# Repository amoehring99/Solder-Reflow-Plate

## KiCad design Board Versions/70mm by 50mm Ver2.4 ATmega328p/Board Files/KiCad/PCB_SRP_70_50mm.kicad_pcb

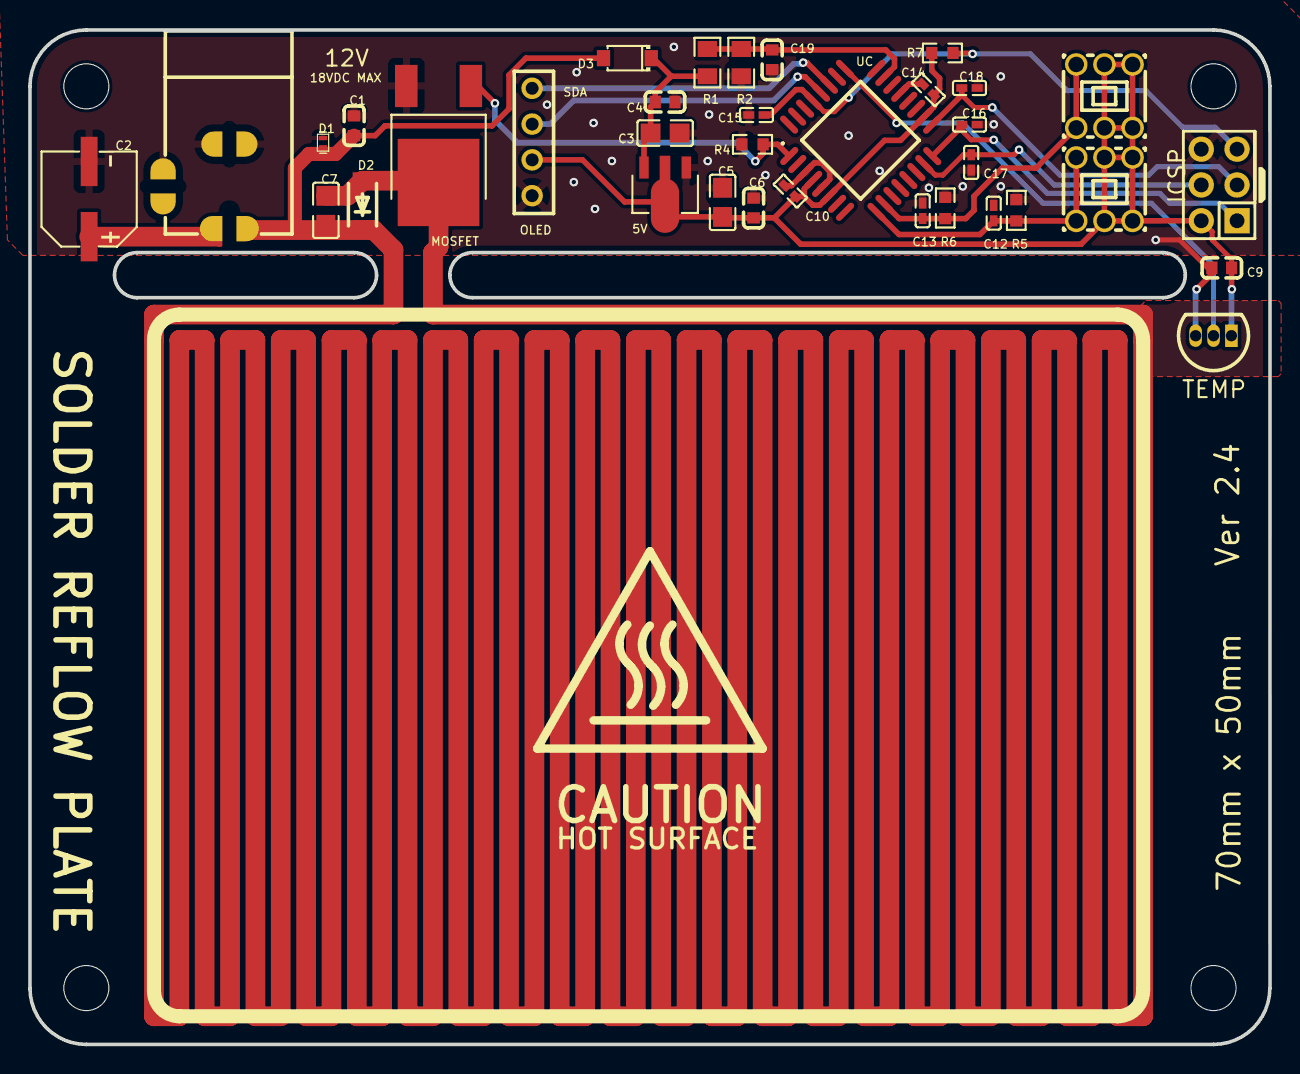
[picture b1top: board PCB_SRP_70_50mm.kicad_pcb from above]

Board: 2 copper layers, 88.0 x 72.0 mm, 35 parts (0 on the bottom side), 15 nets.

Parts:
5V: AMS1117-5.0S; SOT-89_L4.5-W2.5-P1.50-LS4.2-BR
12V: DC-005-5A-2.5; DC-IN-TH_DC-005-5A-2.5
C1, C4, C6, C9, C19: 100nF; C0603
C2: 100uF; CAP-SMD_BD6.3-L6.6-W6.6-LS7.6-FD
C3, C5: 22uF; C0805
C7: 1nF; C0805
C10, C12, C13, C14, C15, C16, C17, C18: 10nF; C0402
D1: PESDMC2FD18VB; SOD-882_L1.0-W0.6-BI
D2: MM1Z24; SOD-123_L2.8-W1.8-LS3.7-FD
D3: DSR1M_C908221; SOD-123_L2.8-W1.8-LS3.7-RD
ICSP: Header-Male-2.54_2x3; HDR-TH_6P-P2.54-V-M-R2-C3-S2.54-1
MOSFET: UMW30N06; TO-252-2_L6.6-W6.1-P4.57-LS9.9-BR-CW
OLED: SDA; OLED_0.91_128X32
R1: 3K; R0805
R2: 1K; R0805
R4, R5, R6, R7: 10K; R0603
SW1, SW2: K8-5851E-N1_C134191; SW-TH_6P-L5.8-W5.8-P2.00-LS4.5-BL
TEMP: LMT85LP; TO-92-3_L4.9-W3.7-P1.27-L
UC: ATMEGA328P-AU; TQFP-32_L7.0-W7.0-P0.80-LS9.0-BL

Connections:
0V: 5V.1, 12V.2, 12V.3, C1.1, C2.2, C3.1, C4.2, C5.1, C6.2, C9.2, C10.2, C12.1, C13.1, C14.1, C15.2, C16.1, C17.1, C18.1, C19.1, D1.1, ICSP.6, MOSFET.3, OLED.4, R2.1, R4.1, R5.2, R6.2, TEMP.3, UC.3, UC.5, UC.21
5V+: 5V.2, C5.2, C6.1, C9.1, C10.1, C14.2, ICSP.2, OLED.3, R7.2, SW1.1, SW1.2, SW1.4, SW1.5, SW2.1, SW2.2, SW2.4, SW2.5, TEMP.1, UC.4, UC.6, UC.18
GATE: MOSFET.1, R4.2, UC.1
MISO: C16.2, ICSP.1, UC.16
MOSI: C17.2, ICSP.4, UC.15
RESET: C15.1, ICSP.5, R7.1, UC.29
SCK: C18.2, ICSP.3, UC.17
SCKOLED: OLED.2, UC.28
SDAOLED: OLED.1, UC.27
SW1: C12.2, R5.1, SW1.3, SW1.6, UC.9
SW2: C13.2, R6.1, SW2.3, SW2.6, UC.10
TEMPDATA: TEMP.2, UC.25
VCC: 12V.1, C1.2, C2.1, C7.1, C7.2, D1.2, D2.1, D2.2, D3.2, MOSFET.2
VCCDIV: C19.2, R1.2, R2.2, UC.23
VIN-D: 5V.3, C3.2, C4.1, D3.1, R1.1

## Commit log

2023-11-01 converted pcb file for kicad
